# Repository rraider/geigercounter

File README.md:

# geigercounter
===

This project is about a simple geigercounter for educational purposes. 

# Versions

## V1.0
This is the first version of the geigercounter.
Its only made of the SBM-20 (a russian tube), the powersupply and a little Piezo, for the recognizable clicking sound.

(Todo: add photos)

## V2.0
The second version uses an Arduino nano and a LCD-panel for displaying the average counts per minute (cpm).

## building instruction (todo)

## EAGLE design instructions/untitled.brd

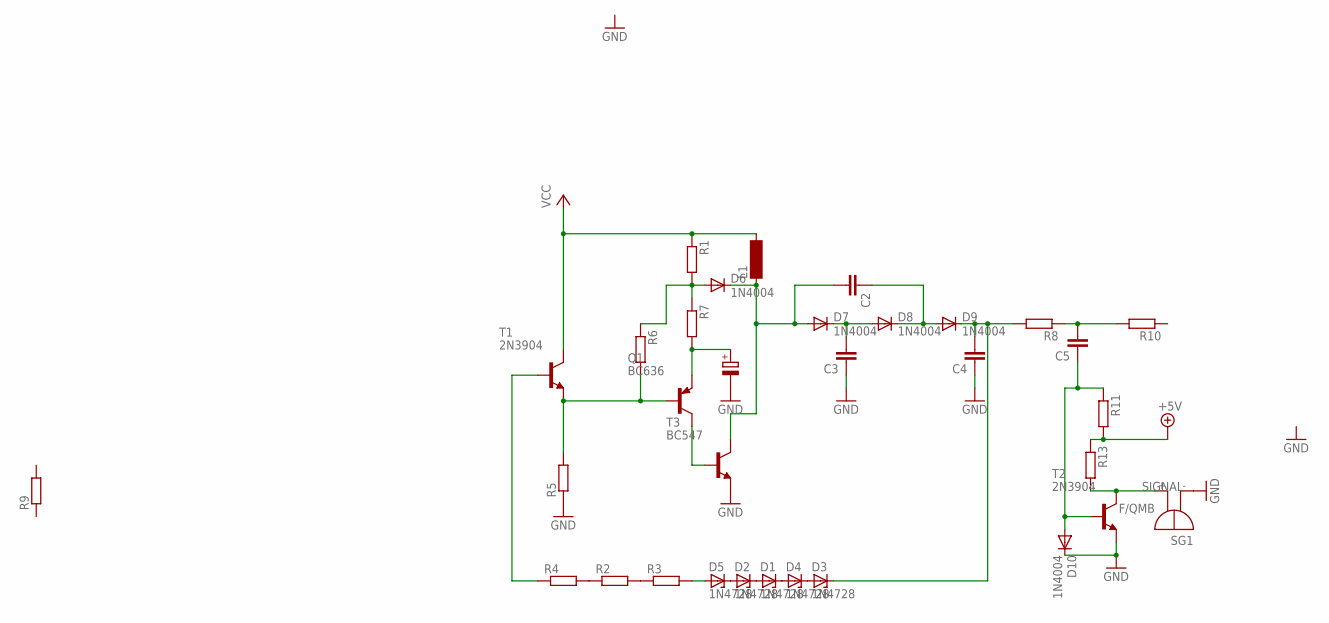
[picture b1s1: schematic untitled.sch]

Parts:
C2, C3, C4, C5: C5/7.2; C5B7.2
D1, D2, D3, D4, D5: 1N4728; DO41Z10
D6, D7, D8, D9, D10: 1N4004; DO41-10
L1: SD8
Q1: BC636; TO92-BCE
R1, R2, R3, R4, R5, R6, R7, R8, R9, R10, R11, R13: R; R0805
SG1: F/QMB
T1, T2: 2N3904; TO92
T3: BC547; TO92

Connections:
+5V: R11.2, R13.1
GND: C3.1, C4.1, D10.C, R5.1, SG1.- (+), T2.3 (E); also elsewhere on the board
unnamed: R2.2, R3.1
unnamed: R2.1, R4.2
unnamed: D5.A, R3.2
unnamed: Q1.B, R5.2, R6.2, T1.3 (E)
unnamed: R4.1, T1.2 (B)
unnamed: D1.A, D2.C
unnamed: D1.C, D4.A
unnamed: D2.A, D5.C
unnamed: D3.A, D4.C
unnamed 11: Q1.E, R7.2; also elsewhere on the board
unnamed: D6.A, R1.2, R6.1, R7.1
unnamed: C2.2, D6.C, D7.A, L1.1, T3.3 (C)
unnamed: Q1.C, T3.2 (B)
unnamed: C3.2, D7.C, D8.A
unnamed: C2.1, D8.C, D9.A
unnamed: C4.2, D3.C, D9.C, R8.2
unnamed: C5.2, R8.1, R10.2
unnamed: C5.1, D10.A, R11.1, T2.2 (B)
unnamed 20: R10.1; also elsewhere on the board
SIGNAL: R13.2, SG1.+ (-), T2.1 (C)
VCC: L1.2, R1.1, T1.1 (C)

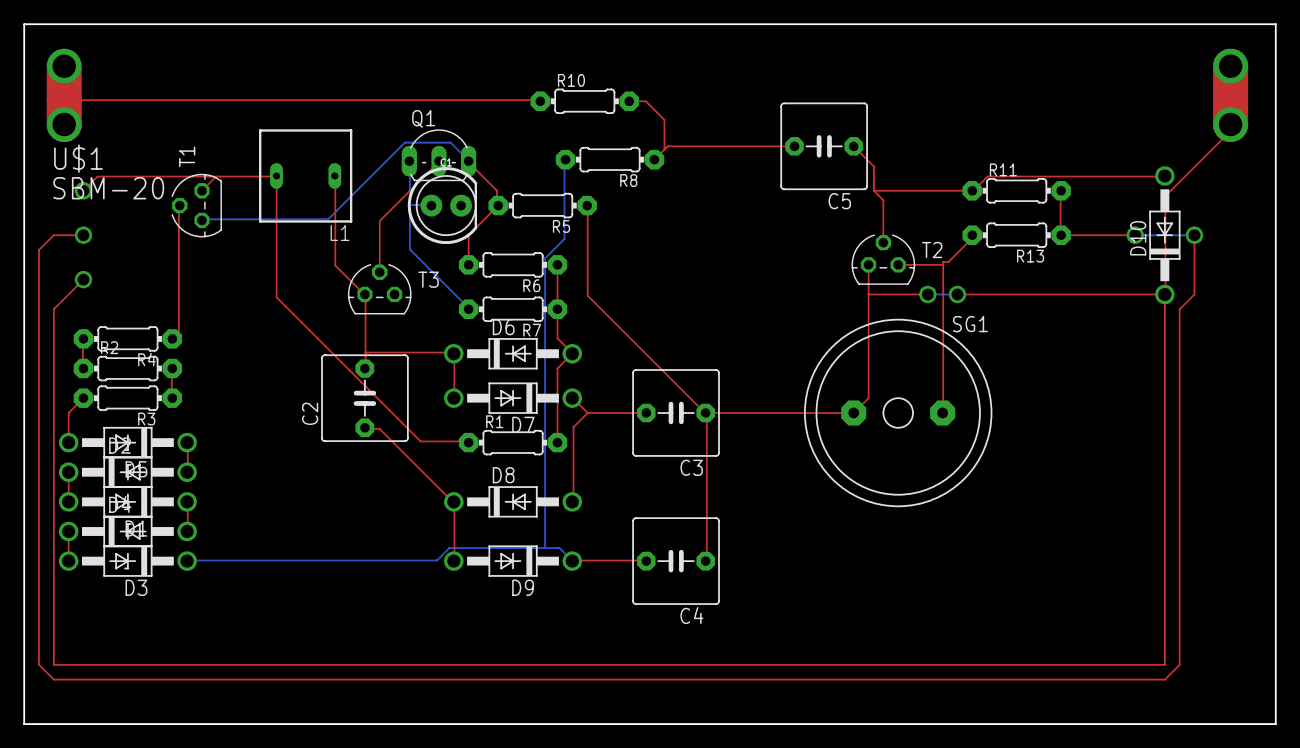
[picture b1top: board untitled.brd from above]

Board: 2 copper layers, 107.3 x 60.0 mm, 33 parts (0 on the bottom side), 23 nets.

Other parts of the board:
C1: LED_5MM
U$1: SBM-20

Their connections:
GND: U$1.P$3, U$1.P$4; also elsewhere on the board
unnamed 11: C1.A; also elsewhere on the board
unnamed 20: U$1.P$1, U$1.P$2; also elsewhere on the board

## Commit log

2018-11-09 added main.ino
2018-11-12 updated instructions
2018-11-15 added new schematic & update instructions
2018-11-15 updated schematic
2018-11-18 added custom lib & updated schematic
2018-11-18 created board.brd

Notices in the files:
parts and their libraries:
SparkFun-LED: Licensing: Creative Commons ShareAlike 4.0 International - https://creativecommons.org/licenses/by-sa/4.0
